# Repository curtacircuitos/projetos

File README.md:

# Curta Circuitos

Projetos em andamento:

* breakout ESP8266, módulo ESP-12-F da AiTinker
* breakout ESP32, módulo usado no beta test
* breakout regulador de tensão 3.3V
* breakout USB-serial
* breakout carregador de bateria íon lítio polímero
  * http://www.microchip.com/wwwproducts/en/en024903 e https://www.maximintegrated.com/en/products/power/battery-management/MAX17044.html

# Referências
 * NodeMCU: https://github.com/nodemcu/nodemcu-devkit
 * Wemos: http://www.wemos.cc/Products/d1_r2.html

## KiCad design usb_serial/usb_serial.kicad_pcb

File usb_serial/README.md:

# Breakout USB-serial

## Status do projeto

Done:
* Esquemático baseado no NodeMCU;
* Footprints definidos com base na BOM disponibilizada;
* Corrigir erros de pin assignment de alguns footprints (e.g. SOT-23 dos transistores) --> Como fazer no KiCad?
	* Edit footprint, clicar nos pads e alterar os números. Salvar em uma nova lib, importá-la no sch e reassign
* Layout v0
* Layout da placa com furos para montagem e silkscreen.

To do:
* Importante: confirmar footprints a serem usados (componentes comerciais mais viáveis).

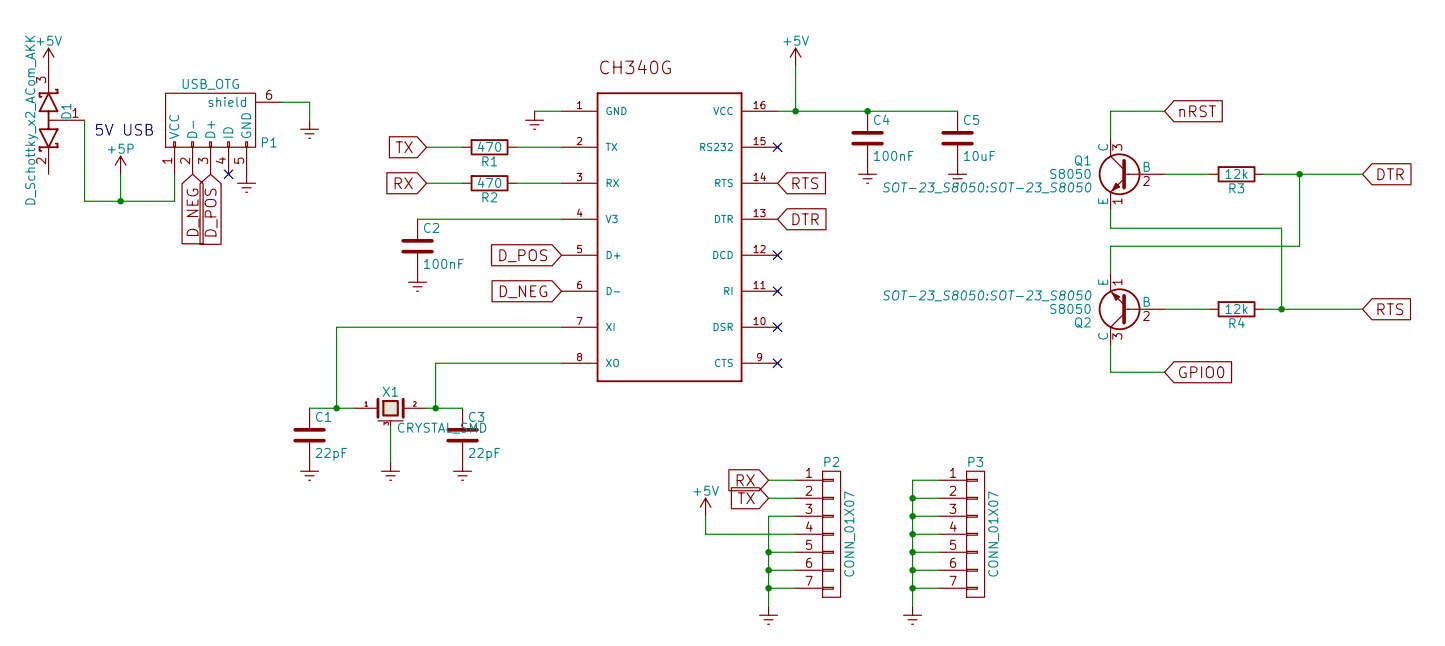
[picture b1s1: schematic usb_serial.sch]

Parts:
C1, C3: 22pF; C_0402
C2, C4: 100nF; C_0402
C5: 10uF; TantalC_SizeB_EIA-3528_HandSoldering
D1: D_Schottky_x2_ACom_AKK; SOT-23
P1: USB_OTG; USB_Micro-B_10103594-0001LF
P2, P3: CONN_01X07; Pin_Header_Straight_1x07
Q1, Q2: S8050; SOT-23_S8050
R1, R2: 470; R_0402
R3, R4: 12k; R_0402
U1: CH340G; SOP-16
X1: CRYSTAL_SMD; Crystal_SMD_2520_4Pads

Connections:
+5P: D1.1 (A), P1.1 (VCC)
+5V: C4.1, C5.1, D1.3 (K), P2.4, U1.16 (VCC)
DTR: Q2.1 (E), R3.1, U1.13 (DTR)
D_NEG: P1.2 (D-), U1.6 (D-)
D_POS: P1.3 (D+), U1.5 (D+)
Earth: C1.2, C2.2, C3.2, C4.2, C5.2, P1.5 (GND), P1.6 (shield), P2.3, P2.5, P2.6, P2.7, P3.1, P3.2, P3.3, P3.4, P3.5, P3.6, P3.7, U1.1 (GND), X1.3 (case)
GPIO0: Q2.3 (C)
unnamed: C1.1, U1.7 (XI), X1.1
unnamed: C2.1, U1.4 (V3)
unnamed: C3.1, U1.8 (XO), X1.2
unnamed: Q1.2 (B), R3.2
unnamed: Q2.2 (B), R4.2
unnamed: R1.1, U1.2 (TX)
unnamed: R2.1, U1.3 (RX)
RTS: Q1.1 (E), R4.1, U1.14 (RTS)
RX: P2.1, R2.2
TX: P2.2, R1.2
nRST: Q1.3 (C)

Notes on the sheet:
5V USB

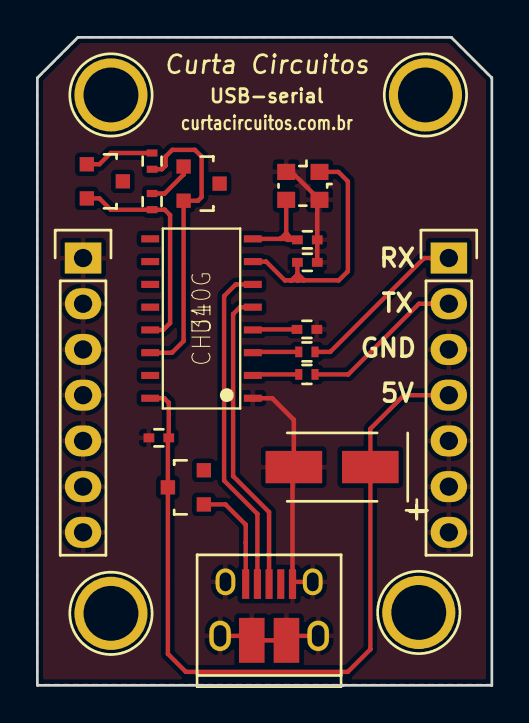
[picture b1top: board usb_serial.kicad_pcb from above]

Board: 2 copper layers, 25.2 x 36.0 mm, 17 parts (0 on the bottom side), 16 nets.

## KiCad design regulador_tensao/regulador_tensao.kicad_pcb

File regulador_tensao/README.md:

# Breakout regulador de tensão 3.3V

## Status do projeto

Done:
* Esquemático baseado no NodeMCU;
* Footprints pré-definidos;
* Primeiro esboço do layout (ver em 3D);
* Layout finalizado com silkscreen.

To do:
* Importante: confirmar footprints a serem usados (componentes comerciais mais viáveis).

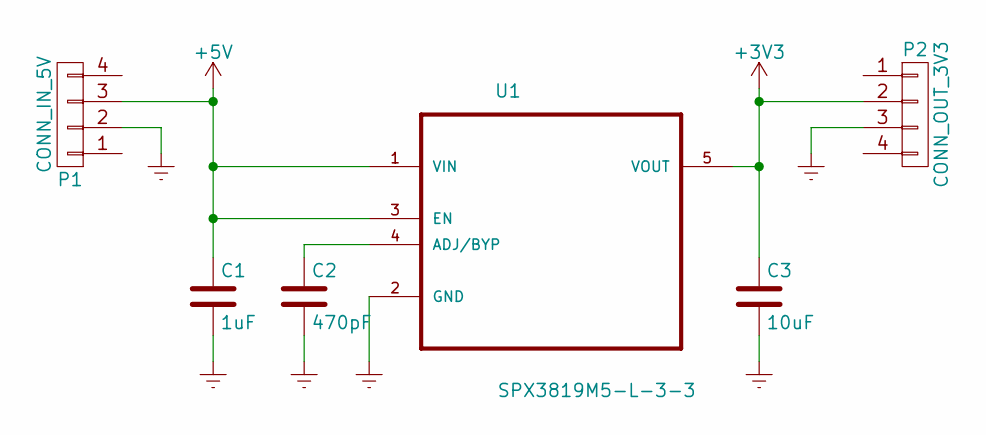
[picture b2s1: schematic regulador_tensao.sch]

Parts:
C1: 1uF; C_0402
C2: 470pF; C_0402
C3: 10uF; C_0402
P1: CONN_IN_5V; Pin_Header_Straight_1x04
P2: CONN_OUT_3V3; Pin_Header_Straight_1x04
U1: SPX3819M5-L-3-3; SOT-23-5

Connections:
+3V3: C3.1, P2.2, U1.5 (VOUT)
+5V: C1.1, P1.3, U1.1 (VIN), U1.3 (EN)
Earth: C1.2, C2.2, C3.2, P1.2, P2.3, U1.2 (GND)
unnamed: C2.1, U1.4 (ADJ/BYP)

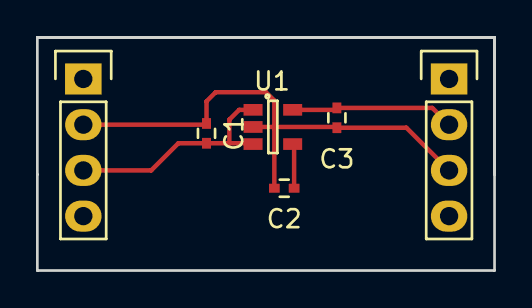
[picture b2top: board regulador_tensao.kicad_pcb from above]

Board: 2 copper layers, 25.4 x 13.0 mm, 6 parts (0 on the bottom side), 4 nets.

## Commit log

2016-03-19 Add datasheet for RS232 converter.
2016-03-19 Added files via upload
2016-03-19 pasta refs adicionada
2016-03-20 Finished schematics. Added refs. PCBs started.
2016-03-20 Fixes in usb footprints. usb/README.md added.
2016-03-20 Updated README.md in subfolders
2016-03-20 Unsaved changes
2016-03-20 To do updated.
2016-03-23 Fixed S8050 footprints. USB PCB v0. Pending GND filled zone.
2016-03-23 usb/README updated.
2016-03-24 Breakout USB v0 done.
2016-03-24 Mounting holes & silkscreen with labels
2016-03-24 3D images added (usb-serial)
2016-03-24 Expanded pin headers and minor fixes. Pics updated.
2016-03-24 Reg. tensao finished, with renderings. Minor fixes in usb-serial
2016-03-24 READMEs updated
